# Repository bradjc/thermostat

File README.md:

thermostat
==========

Hardware and software for interfacing an 802.15.4 radio with a Nest thermostat and Liebert Mini-mate cooling unit.

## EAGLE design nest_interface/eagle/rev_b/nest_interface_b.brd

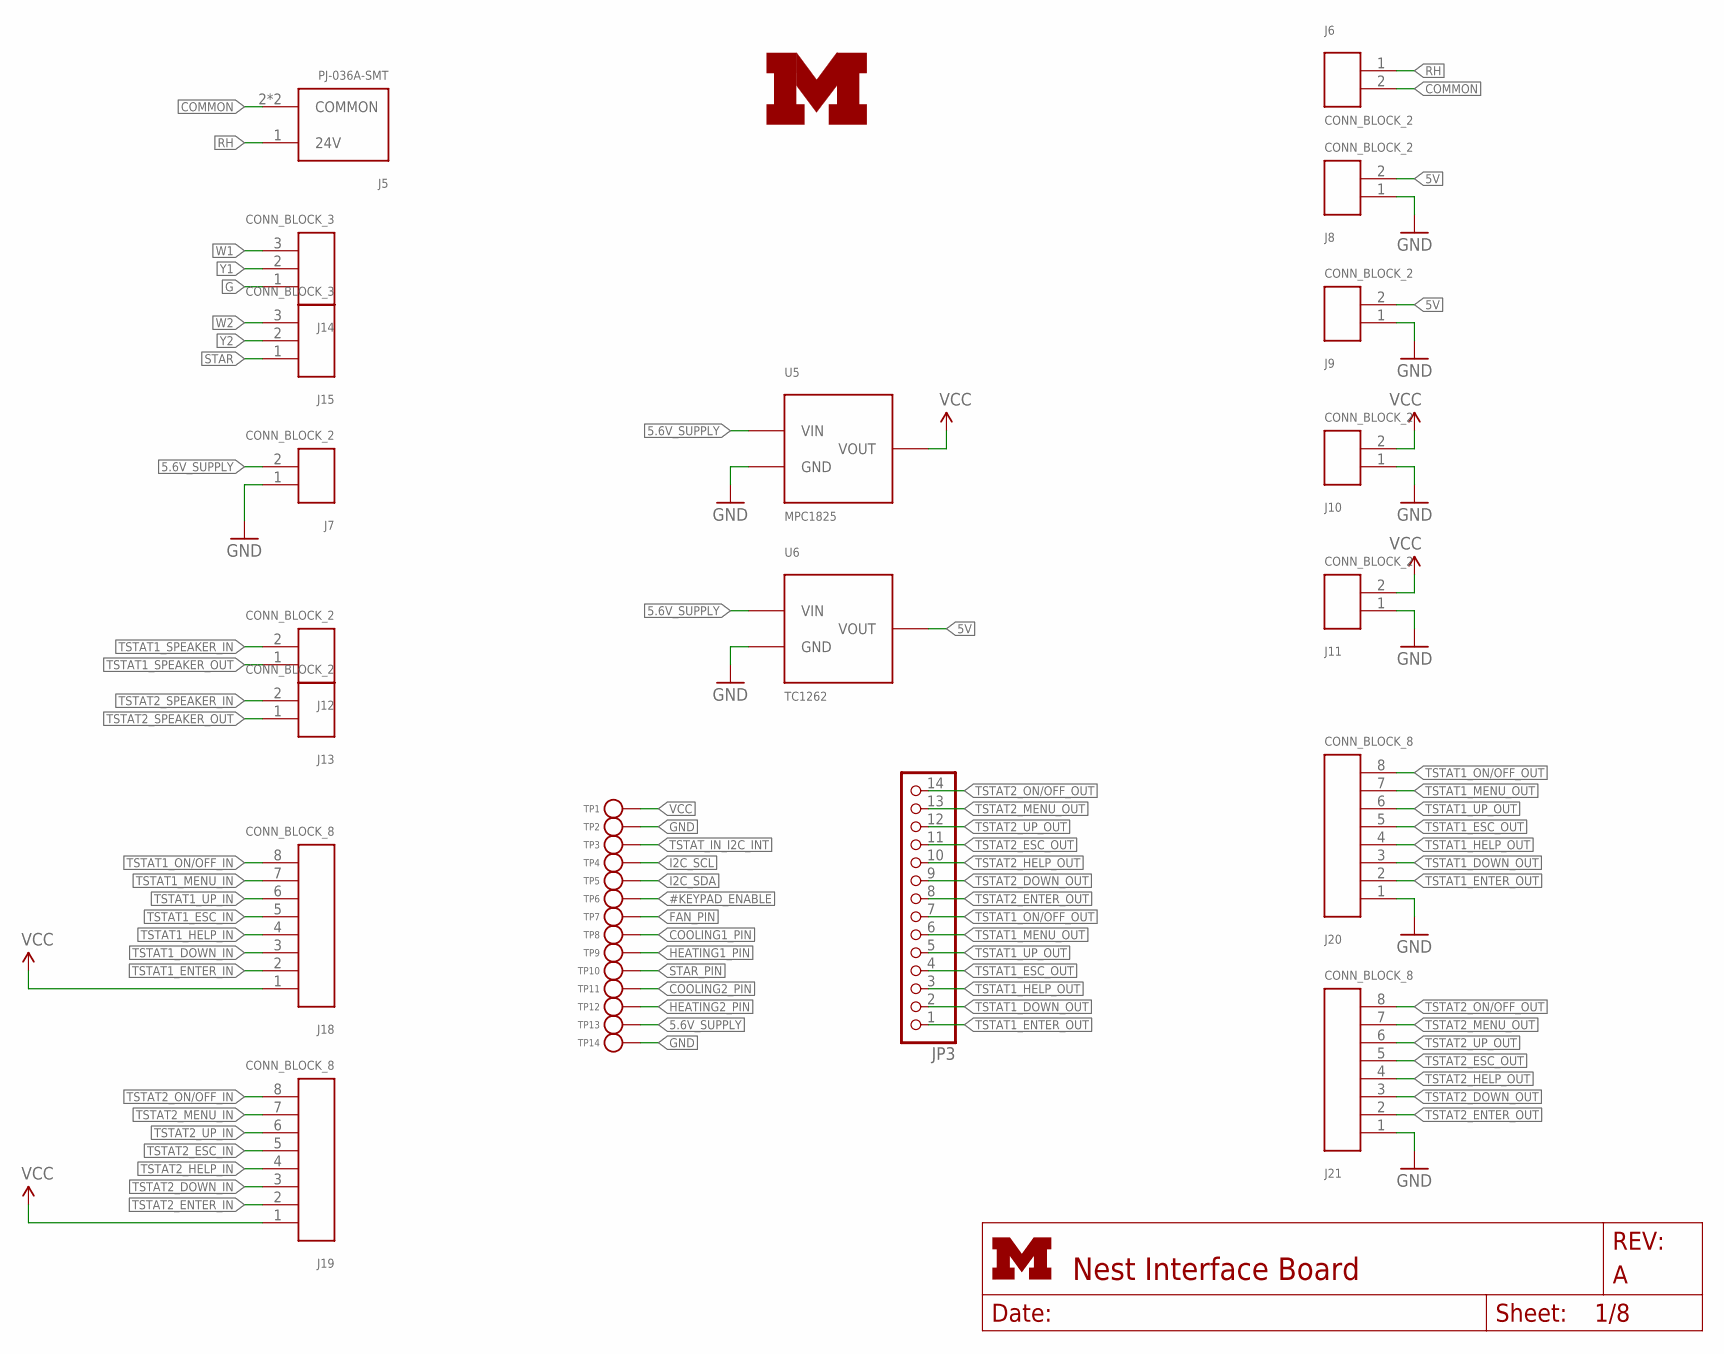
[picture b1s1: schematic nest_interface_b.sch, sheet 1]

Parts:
J5: PJ-036A-SMT; PJ-0361-SMT
J6, J7, J8, J9, J10, J11, J12, J13: CONN_BLOCK_2
J14, J15: CONN_BLOCK_3
J18, J19, J20, J21: CONN_BLOCK_8
JP3: PINHD-1X14; 1X14
TP1, TP2, TP3, TP4, TP5, TP6, TP7, TP8, TP9, TP10, TP11, TP12: TEST_POINT_0.040IN; TESTPOINT_0.040IN
TP13, TP14: TEST_POINT_0.040IN; TESTPOINT_0.040IN; DIGIKEY 5001K-ND
U5: MPC1825; SOT-223-3
U6: TC1262; SOT-223-3
U$1: UMICH_SOLID_LARGE; UMICH_SOLID_350MIL

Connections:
5.6V_SUPPLY: J7.2, TP13.TESTPOINT, U5.1 (VIN), U6.1 (VIN)
5V: J8.2, J9.2, U6.3 (VOUT)
#KEYPAD_ENABLE: TP6.TESTPOINT; also elsewhere on the board
COMMON: J5.2 (COMMON), J5.3 (COMMON), J6.2; also elsewhere on the board
COOLING1_PIN: TP8.TESTPOINT; also elsewhere on the board
COOLING2_PIN: TP11.TESTPOINT; also elsewhere on the board
FAN_PIN: TP7.TESTPOINT; also elsewhere on the board
G: J14.1; also elsewhere on the board
GND: J7.1, J8.1, J9.1, J10.1, J11.1, J20.1, J21.1, TP2.TESTPOINT, TP14.TESTPOINT, U5.2 (GND), U5.4 (GND), U6.2 (GND), U6.4 (GND); also elsewhere on the board
HEATING1_PIN: TP9.TESTPOINT; also elsewhere on the board
HEATING2_PIN: TP12.TESTPOINT; also elsewhere on the board
I2C_SCL: TP4.TESTPOINT; also elsewhere on the board
I2C_SDA: TP5.TESTPOINT; also elsewhere on the board
RH: J5.1 (24V), J6.1
STAR: J15.1; also elsewhere on the board
STAR_PIN: TP10.TESTPOINT; also elsewhere on the board
TSTAT1_DOWN_IN: J18.3; also elsewhere on the board
TSTAT1_DOWN_OUT: J20.3, JP3.2; also elsewhere on the board
TSTAT1_ENTER_IN: J18.2; also elsewhere on the board
TSTAT1_ENTER_OUT: J20.2, JP3.1; also elsewhere on the board
TSTAT1_ESC_IN: J18.5; also elsewhere on the board
TSTAT1_ESC_OUT: J20.5, JP3.4; also elsewhere on the board
TSTAT1_HELP_IN: J18.4; also elsewhere on the board
TSTAT1_HELP_OUT: J20.4, JP3.3; also elsewhere on the board
TSTAT1_MENU_IN: J18.7; also elsewhere on the board
TSTAT1_MENU_OUT: J20.7, JP3.6; also elsewhere on the board
TSTAT1_ON/OFF_IN: J18.8; also elsewhere on the board
TSTAT1_ON/OFF_OUT: J20.8, JP3.7; also elsewhere on the board
TSTAT1_SPEAKER_IN: J12.2; also elsewhere on the board
TSTAT1_SPEAKER_OUT: J12.1; also elsewhere on the board
TSTAT1_UP_IN: J18.6; also elsewhere on the board
TSTAT1_UP_OUT: J20.6, JP3.5; also elsewhere on the board
TSTAT2_DOWN_IN: J19.3; also elsewhere on the board
TSTAT2_DOWN_OUT: J21.3, JP3.9; also elsewhere on the board
TSTAT2_ENTER_IN: J19.2; also elsewhere on the board
TSTAT2_ENTER_OUT: J21.2, JP3.8; also elsewhere on the board
TSTAT2_ESC_IN: J19.5; also elsewhere on the board
TSTAT2_ESC_OUT: J21.5, JP3.11; also elsewhere on the board
TSTAT2_HELP_IN: J19.4; also elsewhere on the board
TSTAT2_HELP_OUT: J21.4, JP3.10; also elsewhere on the board
TSTAT2_MENU_IN: J19.7; also elsewhere on the board
TSTAT2_MENU_OUT: J21.7, JP3.13; also elsewhere on the board
TSTAT2_ON/OFF_IN: J19.8; also elsewhere on the board
TSTAT2_ON/OFF_OUT: J21.8, JP3.14; also elsewhere on the board
TSTAT2_SPEAKER_IN: J13.2; also elsewhere on the board
TSTAT2_SPEAKER_OUT: J13.1; also elsewhere on the board
TSTAT2_UP_IN: J19.6; also elsewhere on the board
TSTAT2_UP_OUT: J21.6, JP3.12; also elsewhere on the board
TSTAT_IN_I2C_INT: TP3.TESTPOINT; also elsewhere on the board
VCC: J10.2, J11.2, J18.1, J19.1, TP1.TESTPOINT, U5.3 (VOUT); also elsewhere on the board
W1: J14.3; also elsewhere on the board
W2: J15.3; also elsewhere on the board
Y1: J14.2; also elsewhere on the board
Y2: J15.2; also elsewhere on the board

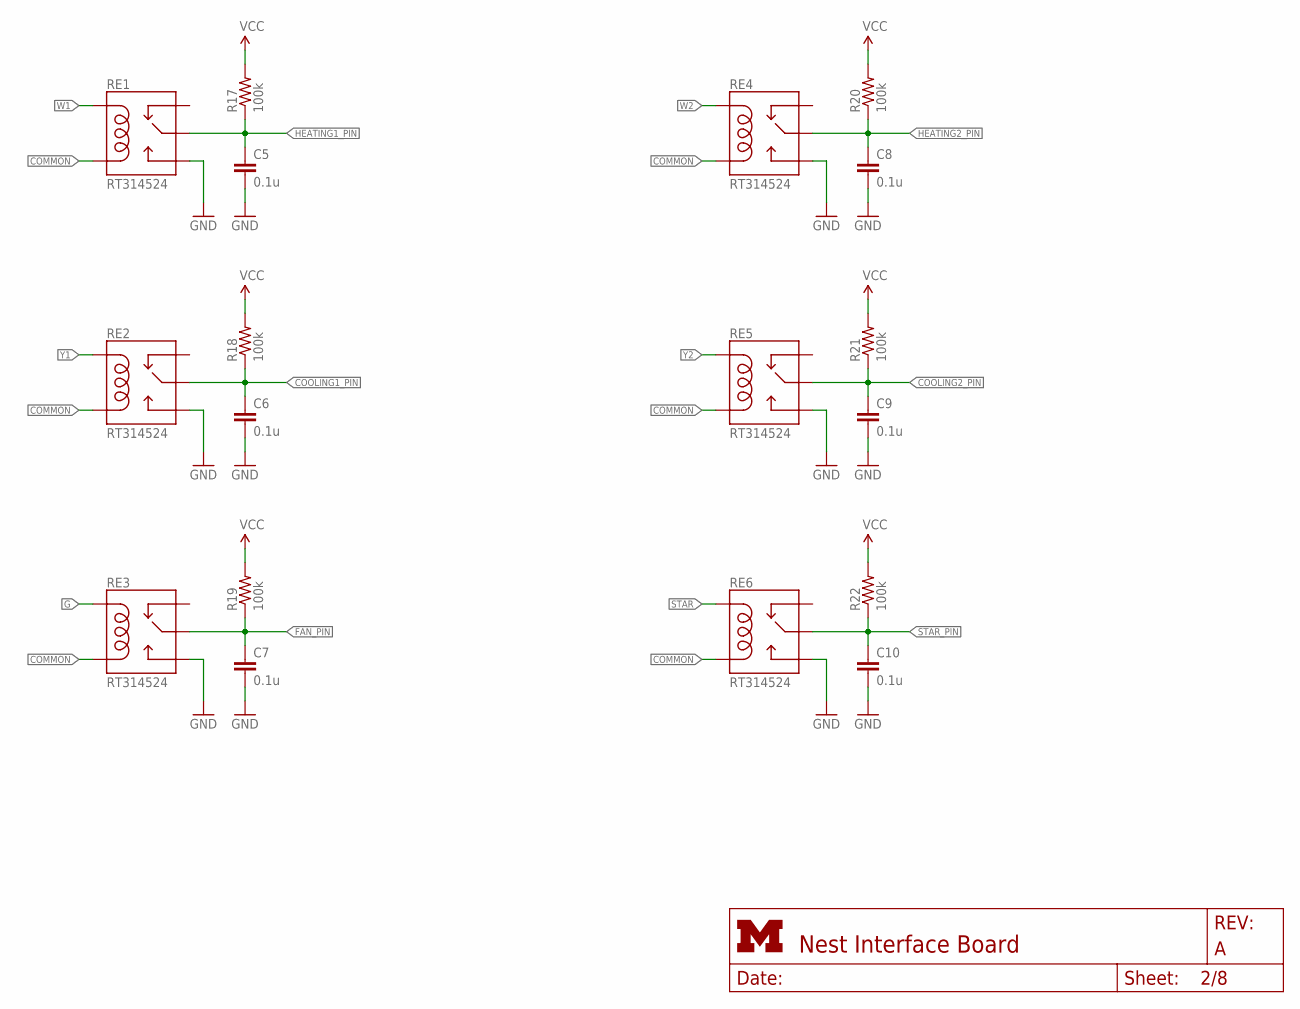
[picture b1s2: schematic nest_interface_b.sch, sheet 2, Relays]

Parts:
C5, C6, C7, C8, C9, C10: 0.1u; C0603
R17, R18, R19, R20, R21, R22: 100k; R0603
RE1, RE2, RE3, RE4, RE5, RE6: RT314524; S0418-CA

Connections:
COMMON: RE1.A2 (COIL2), RE2.A2 (COIL2), RE3.A2 (COIL2), RE4.A2 (COIL2), RE5.A2 (COIL2), RE6.A2 (COIL2); also elsewhere on the board
COOLING1_PIN: C6.1, R18.1, RE2.COMMON1 (MAIN), RE2.COMMON2 (MAIN); also elsewhere on the board
COOLING2_PIN: C9.1, R21.1, RE5.COMMON1 (MAIN), RE5.COMMON2 (MAIN); also elsewhere on the board
FAN_PIN: C7.1, R19.1, RE3.COMMON1 (MAIN), RE3.COMMON2 (MAIN); also elsewhere on the board
G: RE3.A1 (COIL1); also elsewhere on the board
GND: C5.2, C6.2, C7.2, C8.2, C9.2, C10.2, RE1.NO1 (NO), RE1.NO2 (NO), RE2.NO1 (NO), RE2.NO2 (NO), RE3.NO1 (NO), RE3.NO2 (NO), RE4.NO1 (NO), RE4.NO2 (NO), RE5.NO1 (NO), RE5.NO2 (NO), RE6.NO1 (NO), RE6.NO2 (NO); also elsewhere on the board
HEATING1_PIN: C5.1, R17.1, RE1.COMMON1 (MAIN), RE1.COMMON2 (MAIN); also elsewhere on the board
HEATING2_PIN: C8.1, R20.1, RE4.COMMON1 (MAIN), RE4.COMMON2 (MAIN); also elsewhere on the board
STAR: RE6.A1 (COIL1); also elsewhere on the board
STAR_PIN: C10.1, R22.1, RE6.COMMON1 (MAIN), RE6.COMMON2 (MAIN); also elsewhere on the board
VCC: R17.2, R18.2, R19.2, R20.2, R21.2, R22.2; also elsewhere on the board
W1: RE1.A1 (COIL1); also elsewhere on the board
W2: RE4.A1 (COIL1); also elsewhere on the board
Y1: RE2.A1 (COIL1); also elsewhere on the board
Y2: RE5.A1 (COIL1); also elsewhere on the board

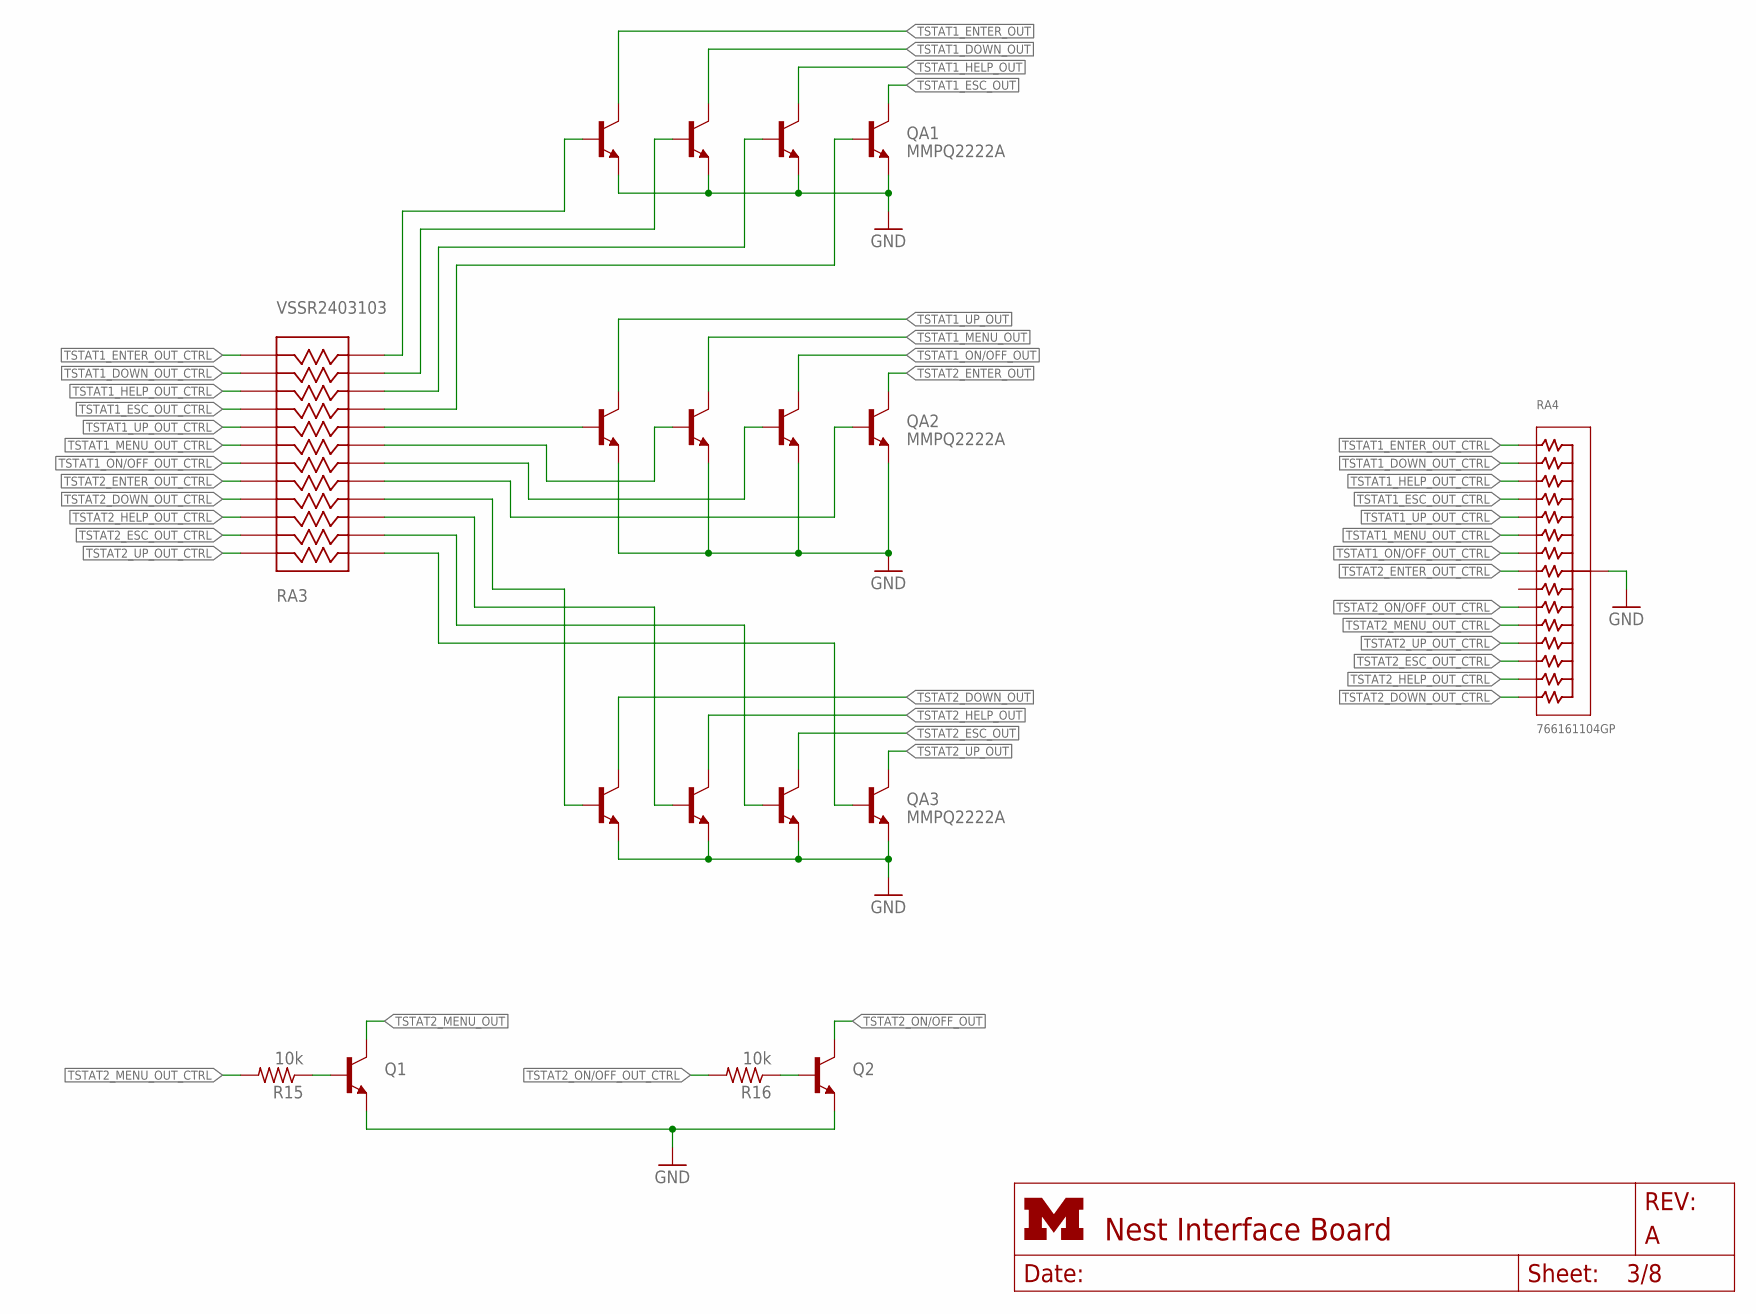
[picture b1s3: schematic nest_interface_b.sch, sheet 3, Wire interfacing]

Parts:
Q1, Q2: TRANSISTOR_NPNSOT23; SOT23; DIGIKEY 568-1636-1-ND
QA1, QA3: MMPQ2222A; SOIC-16; DIGIKEY MMPQ2222ACT-ND
QA2: MMPQ2222A; SOIC-16
R15, R16: 10k; R0603
RA3: VSSR2403103; LSSOP-24
RA4: 766161104GP; SOIC-16

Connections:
GND: Q1.2 (E), Q2.2 (E), QA1.10 (E4), QA1.12 (E3), QA1.14 (E2), QA1.16 (E1), QA2.10 (E4), QA2.12 (E3), QA2.14 (E2), QA2.16 (E1), QA3.10 (E4), QA3.12 (E3), QA3.14 (E2), QA3.16 (E1), RA4.16 (OUT); also elsewhere on the board
unnamed: QA2.11 (B3), RA3.19
unnamed: QA1.13 (B2), RA3.14
unnamed: QA1.11 (B3), RA3.15
unnamed: QA1.9 (B4), RA3.16
unnamed: QA3.9 (B4), RA3.24
unnamed: QA3.15 (B1), RA3.21
unnamed: QA3.13 (B2), RA3.22
unnamed: QA3.11 (B3), RA3.23
unnamed: Q1.1 (B), R15.1
unnamed: Q2.1 (B), R16.1
unnamed: QA1.15 (B1), RA3.13
unnamed: QA2.15 (B1), RA3.17
unnamed: QA2.9 (B4), RA3.20
unnamed: QA2.13 (B2), RA3.18
TSTAT1_DOWN_OUT: QA1.3 (C2), QA1.4 (C2); also elsewhere on the board
TSTAT1_DOWN_OUT_CTRL: RA3.11, RA4.2; also elsewhere on the board
TSTAT1_ENTER_OUT: QA1.1 (C1), QA1.2 (C1); also elsewhere on the board
TSTAT1_ENTER_OUT_CTRL: RA3.12, RA4.1; also elsewhere on the board
TSTAT1_ESC_OUT: QA1.7 (C4), QA1.8 (C4); also elsewhere on the board
TSTAT1_ESC_OUT_CTRL: RA3.9, RA4.4; also elsewhere on the board
TSTAT1_HELP_OUT: QA1.5 (C3), QA1.6 (C3); also elsewhere on the board
TSTAT1_HELP_OUT_CTRL: RA3.10, RA4.3; also elsewhere on the board
TSTAT1_MENU_OUT: QA2.3 (C2), QA2.4 (C2); also elsewhere on the board
TSTAT1_MENU_OUT_CTRL: RA3.7, RA4.6; also elsewhere on the board
TSTAT1_ON/OFF_OUT: QA2.5 (C3), QA2.6 (C3); also elsewhere on the board
TSTAT1_ON/OFF_OUT_CTRL: RA3.6, RA4.7; also elsewhere on the board
TSTAT1_UP_OUT: QA2.1 (C1), QA2.2 (C1); also elsewhere on the board
TSTAT1_UP_OUT_CTRL: RA3.8, RA4.5; also elsewhere on the board
TSTAT2_DOWN_OUT: QA3.1 (C1), QA3.2 (C1); also elsewhere on the board
TSTAT2_DOWN_OUT_CTRL: RA3.4, RA4.15; also elsewhere on the board
TSTAT2_ENTER_OUT: QA2.7 (C4), QA2.8 (C4); also elsewhere on the board
TSTAT2_ENTER_OUT_CTRL: RA3.5, RA4.8; also elsewhere on the board
TSTAT2_ESC_OUT: QA3.5 (C3), QA3.6 (C3); also elsewhere on the board
TSTAT2_ESC_OUT_CTRL: RA3.2, RA4.13; also elsewhere on the board
TSTAT2_HELP_OUT: QA3.3 (C2), QA3.4 (C2); also elsewhere on the board
TSTAT2_HELP_OUT_CTRL: RA3.3, RA4.14; also elsewhere on the board
TSTAT2_MENU_OUT: Q1.3 (C); also elsewhere on the board
TSTAT2_MENU_OUT_CTRL: R15.2, RA4.11; also elsewhere on the board
TSTAT2_ON/OFF_OUT: Q2.3 (C); also elsewhere on the board
TSTAT2_ON/OFF_OUT_CTRL: R16.2, RA4.10; also elsewhere on the board
TSTAT2_UP_OUT: QA3.7 (C4), QA3.8 (C4); also elsewhere on the board
TSTAT2_UP_OUT_CTRL: RA3.1, RA4.12; also elsewhere on the board

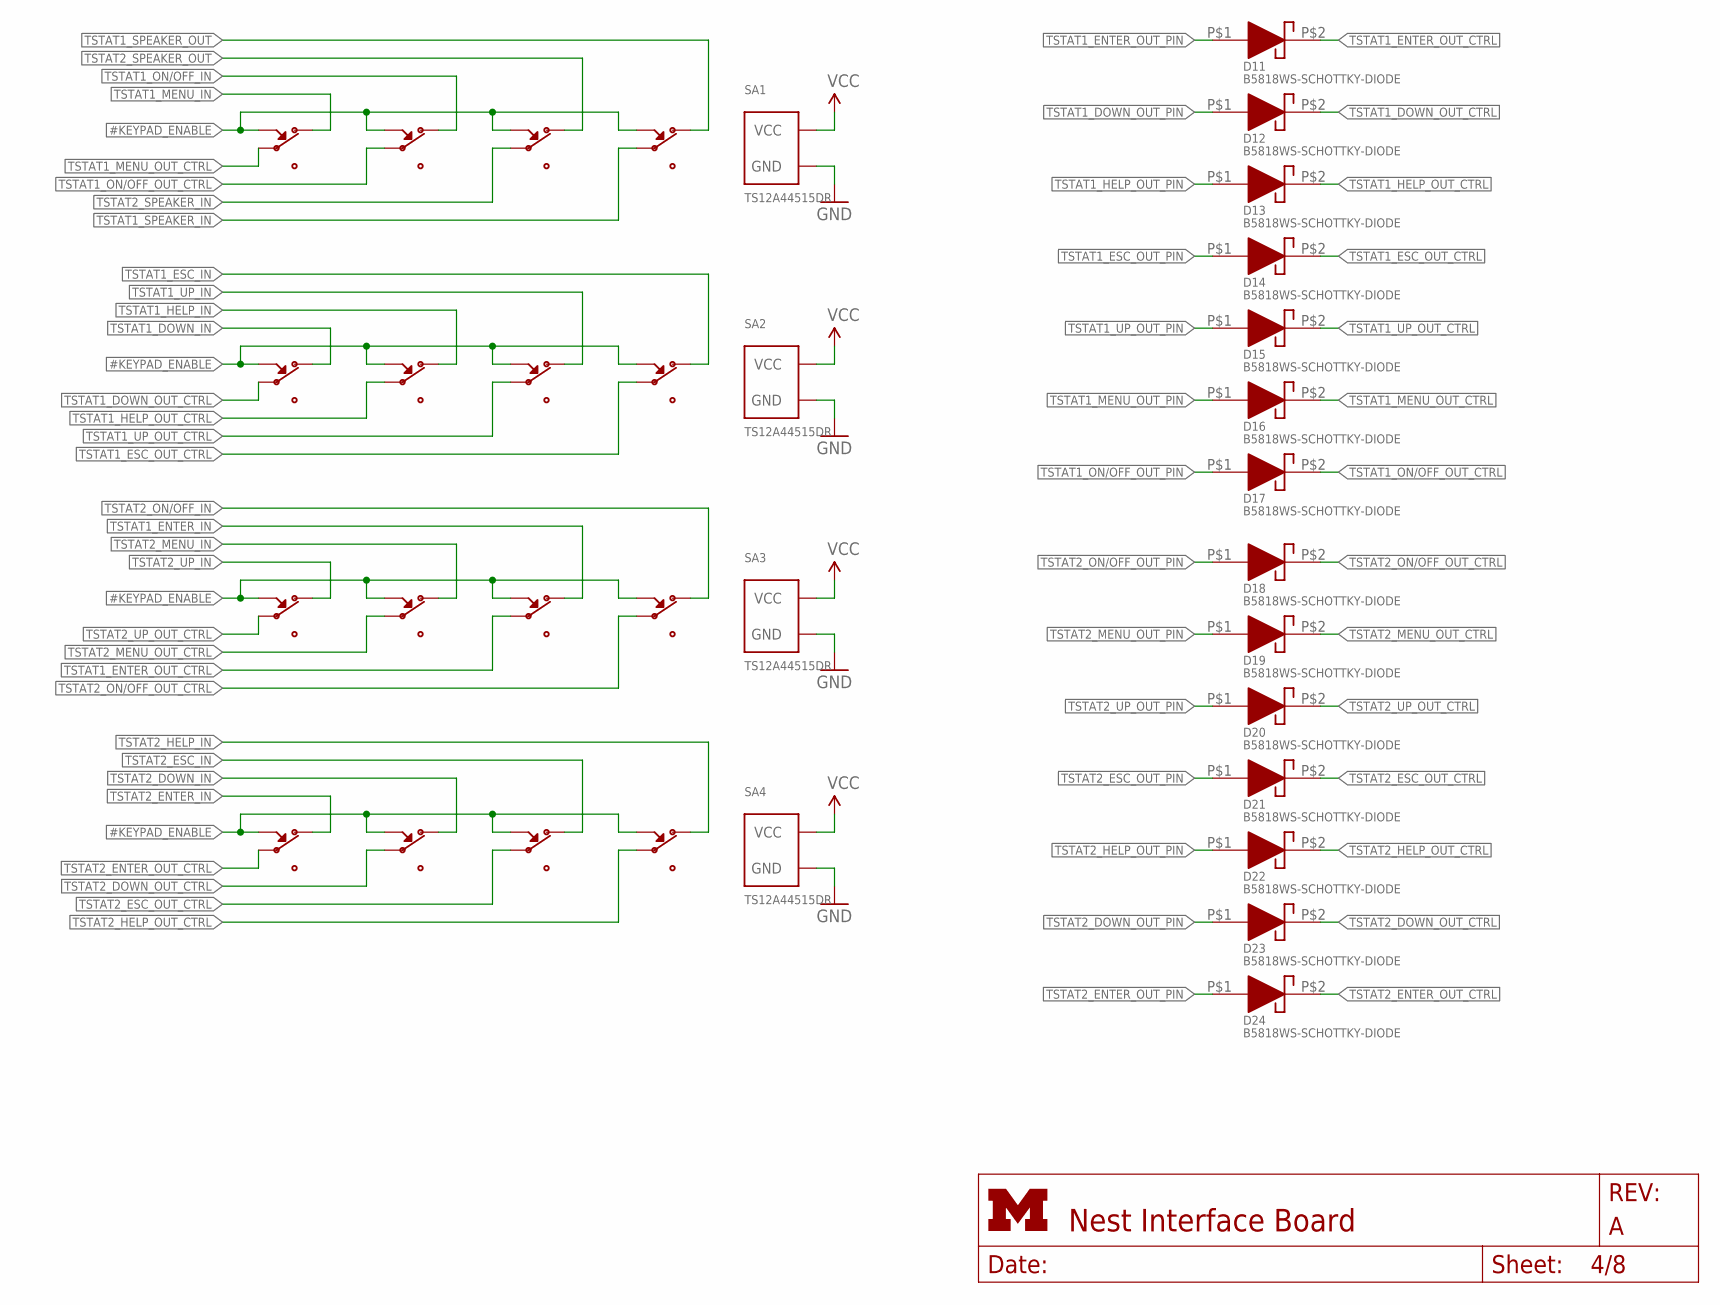
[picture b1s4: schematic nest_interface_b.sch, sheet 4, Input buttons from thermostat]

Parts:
D11, D12, D13, D14, D15, D16, D17, D18, D19, D20, D21, D22, D23, D24: B5818WS-SCHOTTKY-DIODE; SOD-323
SA1, SA2, SA3, SA4: TS12A44515DR; SOIC-14

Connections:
#KEYPAD_ENABLE: SA1.5 (IN2), SA1.6 (IN3), SA1.12 (IN4), SA1.13 (IN1), SA2.5 (IN2), SA2.6 (IN3), SA2.12 (IN4), SA2.13 (IN1), SA3.5 (IN2), SA3.6 (IN3), SA3.12 (IN4), SA3.13 (IN1), SA4.5 (IN2), SA4.6 (IN3), SA4.12 (IN4), SA4.13 (IN1); also elsewhere on the board
GND: SA1.7 (GND), SA2.7 (GND), SA3.7 (GND), SA4.7 (GND); also elsewhere on the board
TSTAT1_DOWN_IN: SA2.1 (NC1); also elsewhere on the board
TSTAT1_DOWN_OUT_CTRL: D12.P$2 (C), SA2.2 (COM1); also elsewhere on the board
TSTAT1_DOWN_OUT_PIN: D12.P$1 (A); also elsewhere on the board
TSTAT1_ENTER_IN: SA3.8 (NC3); also elsewhere on the board
TSTAT1_ENTER_OUT_CTRL: D11.P$2 (C), SA3.9 (COM3); also elsewhere on the board
TSTAT1_ENTER_OUT_PIN: D11.P$1 (A); also elsewhere on the board
TSTAT1_ESC_IN: SA2.11 (NC4); also elsewhere on the board
TSTAT1_ESC_OUT_CTRL: D14.P$2 (C), SA2.10 (COM4); also elsewhere on the board
TSTAT1_ESC_OUT_PIN: D14.P$1 (A); also elsewhere on the board
TSTAT1_HELP_IN: SA2.3 (NC2); also elsewhere on the board
TSTAT1_HELP_OUT_CTRL: D13.P$2 (C), SA2.4 (COM2); also elsewhere on the board
TSTAT1_HELP_OUT_PIN: D13.P$1 (A); also elsewhere on the board
TSTAT1_MENU_IN: SA1.1 (NC1); also elsewhere on the board
TSTAT1_MENU_OUT_CTRL: D16.P$2 (C), SA1.2 (COM1); also elsewhere on the board
TSTAT1_MENU_OUT_PIN: D16.P$1 (A); also elsewhere on the board
TSTAT1_ON/OFF_IN: SA1.3 (NC2); also elsewhere on the board
TSTAT1_ON/OFF_OUT_CTRL: D17.P$2 (C), SA1.4 (COM2); also elsewhere on the board
TSTAT1_ON/OFF_OUT_PIN: D17.P$1 (A); also elsewhere on the board
TSTAT1_SPEAKER_IN: SA1.10 (COM4); also elsewhere on the board
TSTAT1_SPEAKER_OUT: SA1.11 (NC4); also elsewhere on the board
TSTAT1_UP_IN: SA2.8 (NC3); also elsewhere on the board
TSTAT1_UP_OUT_CTRL: D15.P$2 (C), SA2.9 (COM3); also elsewhere on the board
TSTAT1_UP_OUT_PIN: D15.P$1 (A); also elsewhere on the board
TSTAT2_DOWN_IN: SA4.3 (NC2); also elsewhere on the board
TSTAT2_DOWN_OUT_CTRL: D23.P$2 (C), SA4.4 (COM2); also elsewhere on the board
TSTAT2_DOWN_OUT_PIN: D23.P$1 (A); also elsewhere on the board
TSTAT2_ENTER_IN: SA4.1 (NC1); also elsewhere on the board
TSTAT2_ENTER_OUT_CTRL: D24.P$2 (C), SA4.2 (COM1); also elsewhere on the board
TSTAT2_ENTER_OUT_PIN: D24.P$1 (A); also elsewhere on the board
TSTAT2_ESC_IN: SA4.8 (NC3); also elsewhere on the board
TSTAT2_ESC_OUT_CTRL: D21.P$2 (C), SA4.9 (COM3); also elsewhere on the board
TSTAT2_ESC_OUT_PIN: D21.P$1 (A); also elsewhere on the board
TSTAT2_HELP_IN: SA4.11 (NC4); also elsewhere on the board
TSTAT2_HELP_OUT_CTRL: D22.P$2 (C), SA4.10 (COM4); also elsewhere on the board
TSTAT2_HELP_OUT_PIN: D22.P$1 (A); also elsewhere on the board
TSTAT2_MENU_IN: SA3.3 (NC2); also elsewhere on the board
TSTAT2_MENU_OUT_CTRL: D19.P$2 (C), SA3.4 (COM2); also elsewhere on the board
TSTAT2_MENU_OUT_PIN: D19.P$1 (A); also elsewhere on the board
TSTAT2_ON/OFF_IN: SA3.11 (NC4); also elsewhere on the board
TSTAT2_ON/OFF_OUT_CTRL: D18.P$2 (C), SA3.10 (COM4); also elsewhere on the board
TSTAT2_ON/OFF_OUT_PIN: D18.P$1 (A); also elsewhere on the board
TSTAT2_SPEAKER_IN: SA1.9 (COM3); also elsewhere on the board
TSTAT2_SPEAKER_OUT: SA1.8 (NC3); also elsewhere on the board
TSTAT2_UP_IN: SA3.1 (NC1); also elsewhere on the board
TSTAT2_UP_OUT_CTRL: D20.P$2 (C), SA3.2 (COM1); also elsewhere on the board
TSTAT2_UP_OUT_PIN: D20.P$1 (A); also elsewhere on the board
VCC: SA1.14 (VCC), SA2.14 (VCC), SA3.14 (VCC), SA4.14 (VCC); also elsewhere on the board

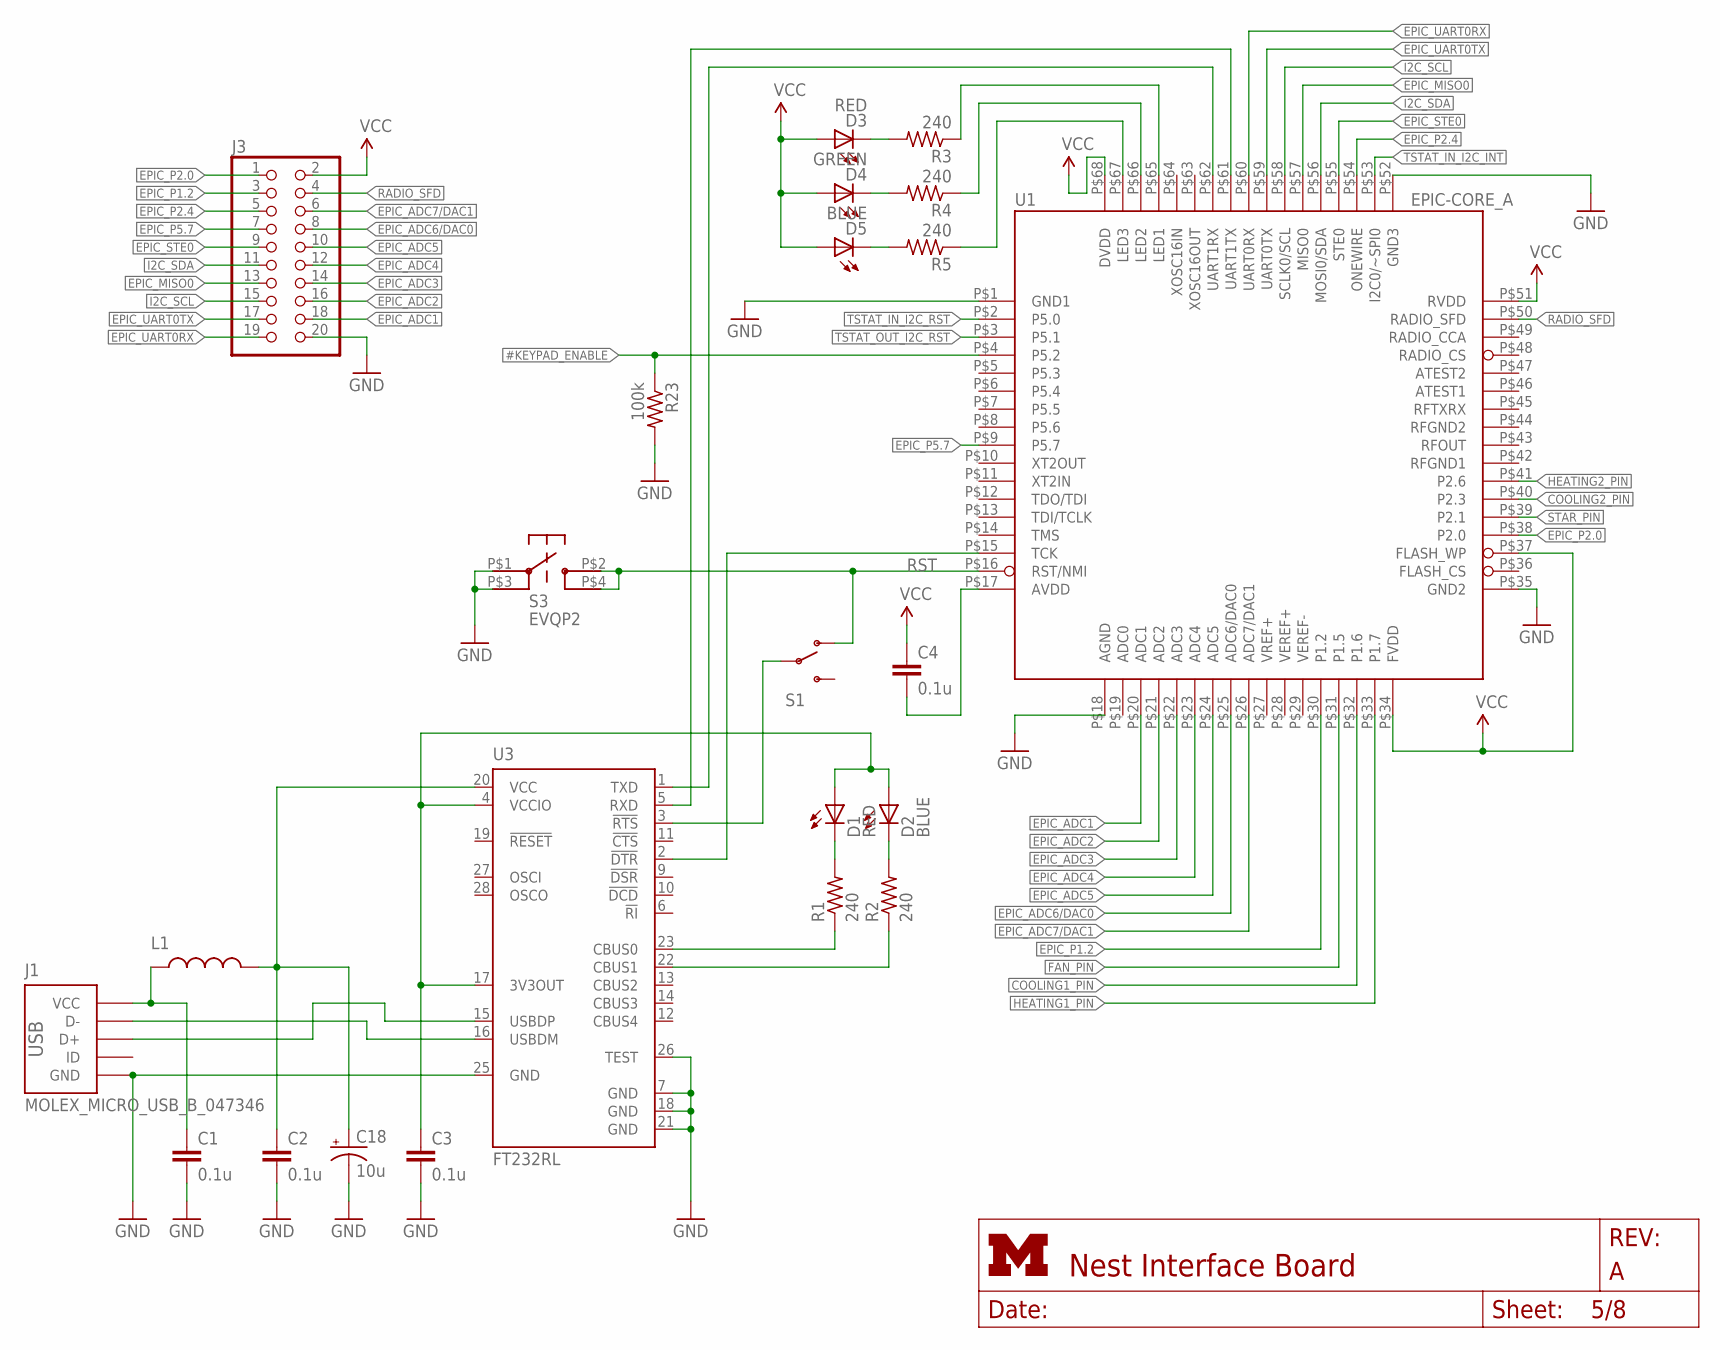
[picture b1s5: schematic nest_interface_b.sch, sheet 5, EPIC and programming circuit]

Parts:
C1, C2, C3, C4: 0.1u; C0603
C18: 10u; EIA3216; DIGIKEY 478-1655-1-ND
D1, D3: RED; LED-0603
D2, D5: BLUE; LED-0603
D4: GREEN; LED-0603
J1: MOLEX_MICRO_USB_B_047346
J3: PINHD-2X10; 2X10
L1: INDUCTOR0603; 0603; DIGIKEY 240-2373-1-ND
R1, R2, R3, R4, R5: 240; R0603
R23: 100k; R0603
S1: SWITCH-SPSTPTH; SWITCH-SPDT; DIGIKEY EG1903-ND
S3: EVQP2; DIGIKEY P11084SCT-ND
U1: EPIC-CORE_A; EPIC-LCC68
U3: FT232RL; SSOP28; DIGIKEY 768-1007-1-ND

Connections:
#KEYPAD_ENABLE: R23.1, U1.P$4 (P5.2); also elsewhere on the board
COOLING1_PIN: U1.P$32 (P1.6); also elsewhere on the board
COOLING2_PIN: U1.P$40 (P2.3); also elsewhere on the board
EPIC_ADC1: J3.18, U1.P$20 (ADC1)
EPIC_ADC2: J3.16, U1.P$21 (ADC2)
EPIC_ADC3: J3.14, U1.P$22 (ADC3)
EPIC_ADC4: J3.12, U1.P$23 (ADC4)
EPIC_ADC5: J3.10, U1.P$24 (ADC5)
EPIC_ADC6/DAC0: J3.8, U1.P$25 (ADC6/DAC0)
EPIC_ADC7/DAC1: J3.6, U1.P$26 (ADC7/DAC1)
EPIC_MISO0: J3.13, U1.P$57 (MISO0)
EPIC_P1.2: J3.3, U1.P$30 (P1.2)
EPIC_P2.0: J3.1, U1.P$38 (P2.0)
EPIC_P2.4: J3.5, U1.P$54 (ONEWIRE)
EPIC_P5.7: J3.7, U1.P$9 (P5.7)
EPIC_STE0: J3.9, U1.P$55 (STE0)
EPIC_UART0RX: J3.19, U1.P$60 (UART0RX)
EPIC_UART0TX: J3.17, U1.P$59 (UART0TX)
FAN_PIN: U1.P$31 (P1.5); also elsewhere on the board
GND: C1.2, C2.2, C3.2, C18.C (-), J1.GND, J3.20, R23.2, S3.P$1, S3.P$3, U1.P$1 (GND1), U1.P$18 (AGND), U1.P$35 (GND2), U1.P$52 (GND3), U3.7 (GND), U3.18 (GND), U3.21 (GND), U3.25 (GND), U3.26 (TEST); also elsewhere on the board
HEATING1_PIN: U1.P$33 (P1.7); also elsewhere on the board
HEATING2_PIN: U1.P$41 (P2.6); also elsewhere on the board
I2C_SCL: J3.15, U1.P$58 (SCLK0/SCL); also elsewhere on the board
I2C_SDA: J3.11, U1.P$56 (MOSI0/SDA); also elsewhere on the board
unnamed: C1.1, J1.VCC, L1.1
unnamed: D1.C, R1.2
unnamed: J1.D-, U3.16 (USBDM)
unnamed: J1.D+, U3.15 (USBDP)
unnamed: C2.1, C18.A (+), L1.2, U3.20 (VCC)
unnamed: D2.C, R2.2
unnamed: U1.P$62 (UART1RX), U3.1 (TXD)
unnamed: R1.1, U3.23 (CBUS0)
unnamed: R2.1, U3.22 (CBUS1)
unnamed: U1.P$61 (UART1TX), U3.5 (RXD)
unnamed: U1.P$15 (TCK), U3.2 (!DTR)
unnamed: C3.1, D1.A, D2.A, U3.4 (VCCIO), U3.17 (3V3OUT)
unnamed: C4.2, U1.P$17 (AVDD)
unnamed: D3.C, R3.2
unnamed: D4.C, R4.2
unnamed: D5.C, R5.2
unnamed: R5.1, U1.P$67 (LED3)
unnamed: R4.1, U1.P$66 (LED2)
unnamed: R3.1, U1.P$65 (LED1)
RADIO_SFD: J3.4, U1.P$50 (RADIO_SFD)
RST: S1.1 (O), S3.P$2, S3.P$4, U1.P$16 (RST/NMI)
RST_USB: S1.2, U3.3 (!RTS)
STAR_PIN: U1.P$39 (P2.1); also elsewhere on the board
TSTAT_IN_I2C_INT: U1.P$53 (I2C0/~SPI0); also elsewhere on the board
TSTAT_IN_I2C_RST: U1.P$2 (P5.0); also elsewhere on the board
TSTAT_OUT_I2C_RST: U1.P$3 (P5.1); also elsewhere on the board
VCC: C4.1, D3.A, D4.A, D5.A, J3.2, U1.P$34 (FVDD), U1.P$37 (FLASH_WP), U1.P$51 (RVDD), U1.P$68 (DVDD); also elsewhere on the board

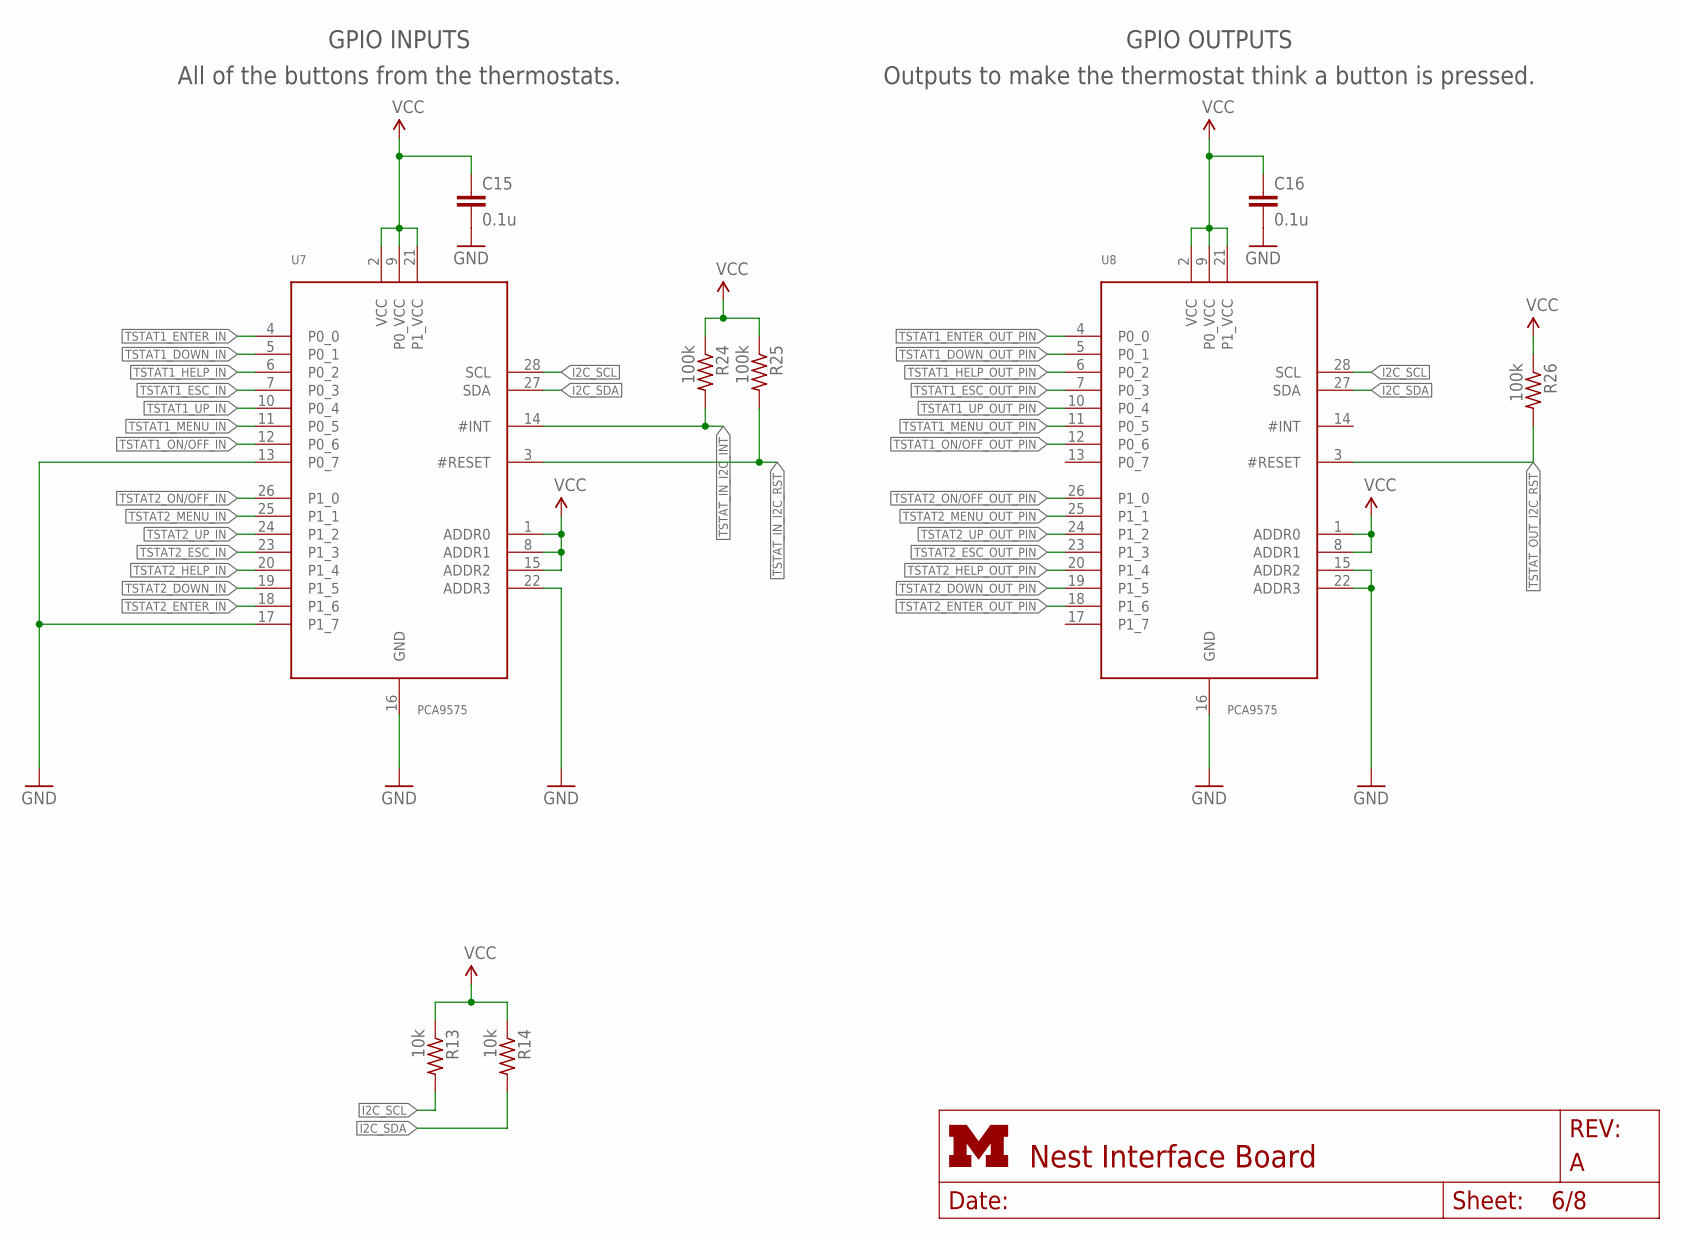
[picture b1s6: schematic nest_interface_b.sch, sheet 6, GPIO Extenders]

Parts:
C15, C16: 0.1u; C0603
R13, R14: 10k; R0603
R24, R25, R26: 100k; R0603
U7, U8: PCA9575; TSSOP28

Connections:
GND: C15.2, C16.2, U7.13 (P0_7), U7.16 (GND), U7.17 (P1_7), U7.22 (ADDR3), U8.15 (ADDR2), U8.16 (GND), U8.22 (ADDR3); also elsewhere on the board
I2C_SCL: R13.2, U7.28 (SCL), U8.28 (SCL); also elsewhere on the board
I2C_SDA: R14.2, U7.27 (SDA), U8.27 (SDA); also elsewhere on the board
TSTAT1_DOWN_IN: U7.5 (P0_1); also elsewhere on the board
TSTAT1_DOWN_OUT_PIN: U8.5 (P0_1); also elsewhere on the board
TSTAT1_ENTER_IN: U7.4 (P0_0); also elsewhere on the board
TSTAT1_ENTER_OUT_PIN: U8.4 (P0_0); also elsewhere on the board
TSTAT1_ESC_IN: U7.7 (P0_3); also elsewhere on the board
TSTAT1_ESC_OUT_PIN: U8.7 (P0_3); also elsewhere on the board
TSTAT1_HELP_IN: U7.6 (P0_2); also elsewhere on the board
TSTAT1_HELP_OUT_PIN: U8.6 (P0_2); also elsewhere on the board
TSTAT1_MENU_IN: U7.11 (P0_5); also elsewhere on the board
TSTAT1_MENU_OUT_PIN: U8.11 (P0_5); also elsewhere on the board
TSTAT1_ON/OFF_IN: U7.12 (P0_6); also elsewhere on the board
TSTAT1_ON/OFF_OUT_PIN: U8.12 (P0_6); also elsewhere on the board
TSTAT1_UP_IN: U7.10 (P0_4); also elsewhere on the board
TSTAT1_UP_OUT_PIN: U8.10 (P0_4); also elsewhere on the board
TSTAT2_DOWN_IN: U7.19 (P1_5); also elsewhere on the board
TSTAT2_DOWN_OUT_PIN: U8.19 (P1_5); also elsewhere on the board
TSTAT2_ENTER_IN: U7.18 (P1_6); also elsewhere on the board
TSTAT2_ENTER_OUT_PIN: U8.18 (P1_6); also elsewhere on the board
TSTAT2_ESC_IN: U7.23 (P1_3); also elsewhere on the board
TSTAT2_ESC_OUT_PIN: U8.23 (P1_3); also elsewhere on the board
TSTAT2_HELP_IN: U7.20 (P1_4); also elsewhere on the board
TSTAT2_HELP_OUT_PIN: U8.20 (P1_4); also elsewhere on the board
TSTAT2_MENU_IN: U7.25 (P1_1); also elsewhere on the board
TSTAT2_MENU_OUT_PIN: U8.25 (P1_1); also elsewhere on the board
TSTAT2_ON/OFF_IN: U7.26 (P1_0); also elsewhere on the board
TSTAT2_ON/OFF_OUT_PIN: U8.26 (P1_0); also elsewhere on the board
TSTAT2_UP_IN: U7.24 (P1_2); also elsewhere on the board
TSTAT2_UP_OUT_PIN: U8.24 (P1_2); also elsewhere on the board
TSTAT_IN_I2C_INT: R24.2, U7.14 (#INT); also elsewhere on the board
TSTAT_IN_I2C_RST: R25.2, U7.3 (#RESET); also elsewhere on the board
TSTAT_OUT_I2C_RST: R26.2, U8.3 (#RESET); also elsewhere on the board
VCC: C15.1, C16.1, R13.1, R14.1, R24.1, R25.1, R26.1, U7.1 (ADDR0), U7.2 (VCC), U7.8 (ADDR1), U7.9 (P0_VCC), U7.15 (ADDR2), U7.21 (P1_VCC), U8.1 (ADDR0), U8.2 (VCC), U8.8 (ADDR1), U8.9 (P0_VCC), U8.21 (P1_VCC); also elsewhere on the board

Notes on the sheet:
GPIO INPUTS
All of the buttons from the thermostats.
GPIO OUTPUTS
Outputs to make the thermostat think a button is pressed.

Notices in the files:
parts and their libraries:
SparkFun: Licensing: CC v3.0 Share-Alike You are welcome to use this library for commercial purposes.
